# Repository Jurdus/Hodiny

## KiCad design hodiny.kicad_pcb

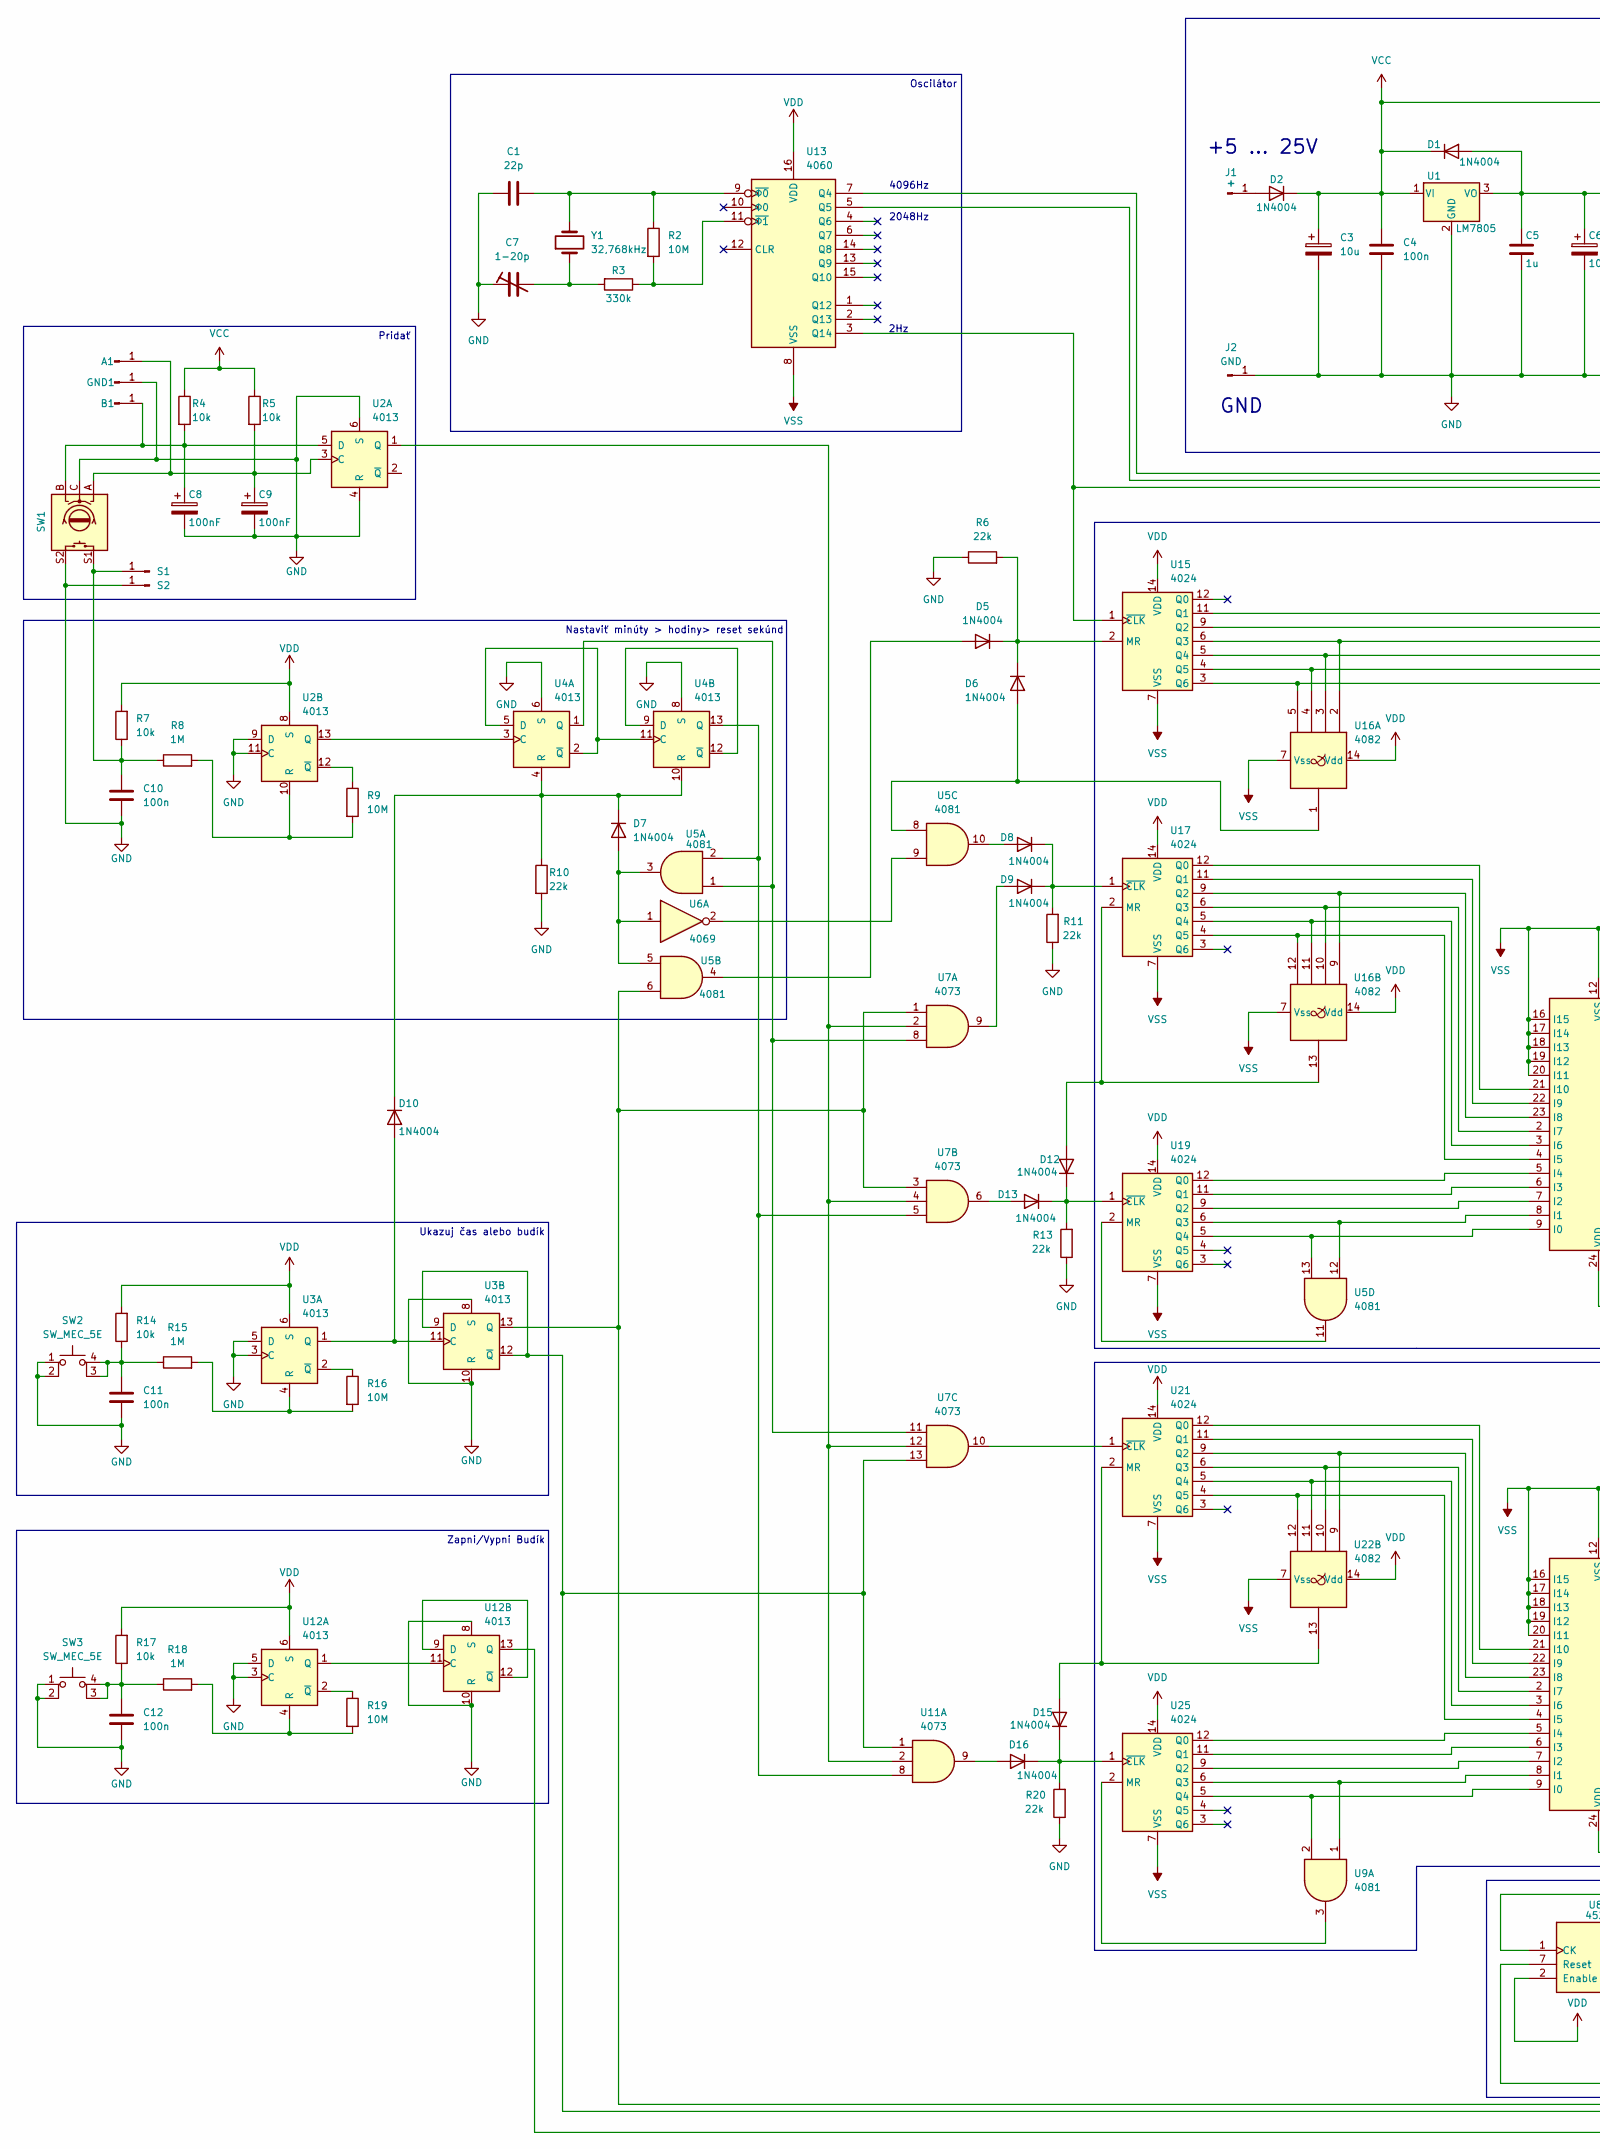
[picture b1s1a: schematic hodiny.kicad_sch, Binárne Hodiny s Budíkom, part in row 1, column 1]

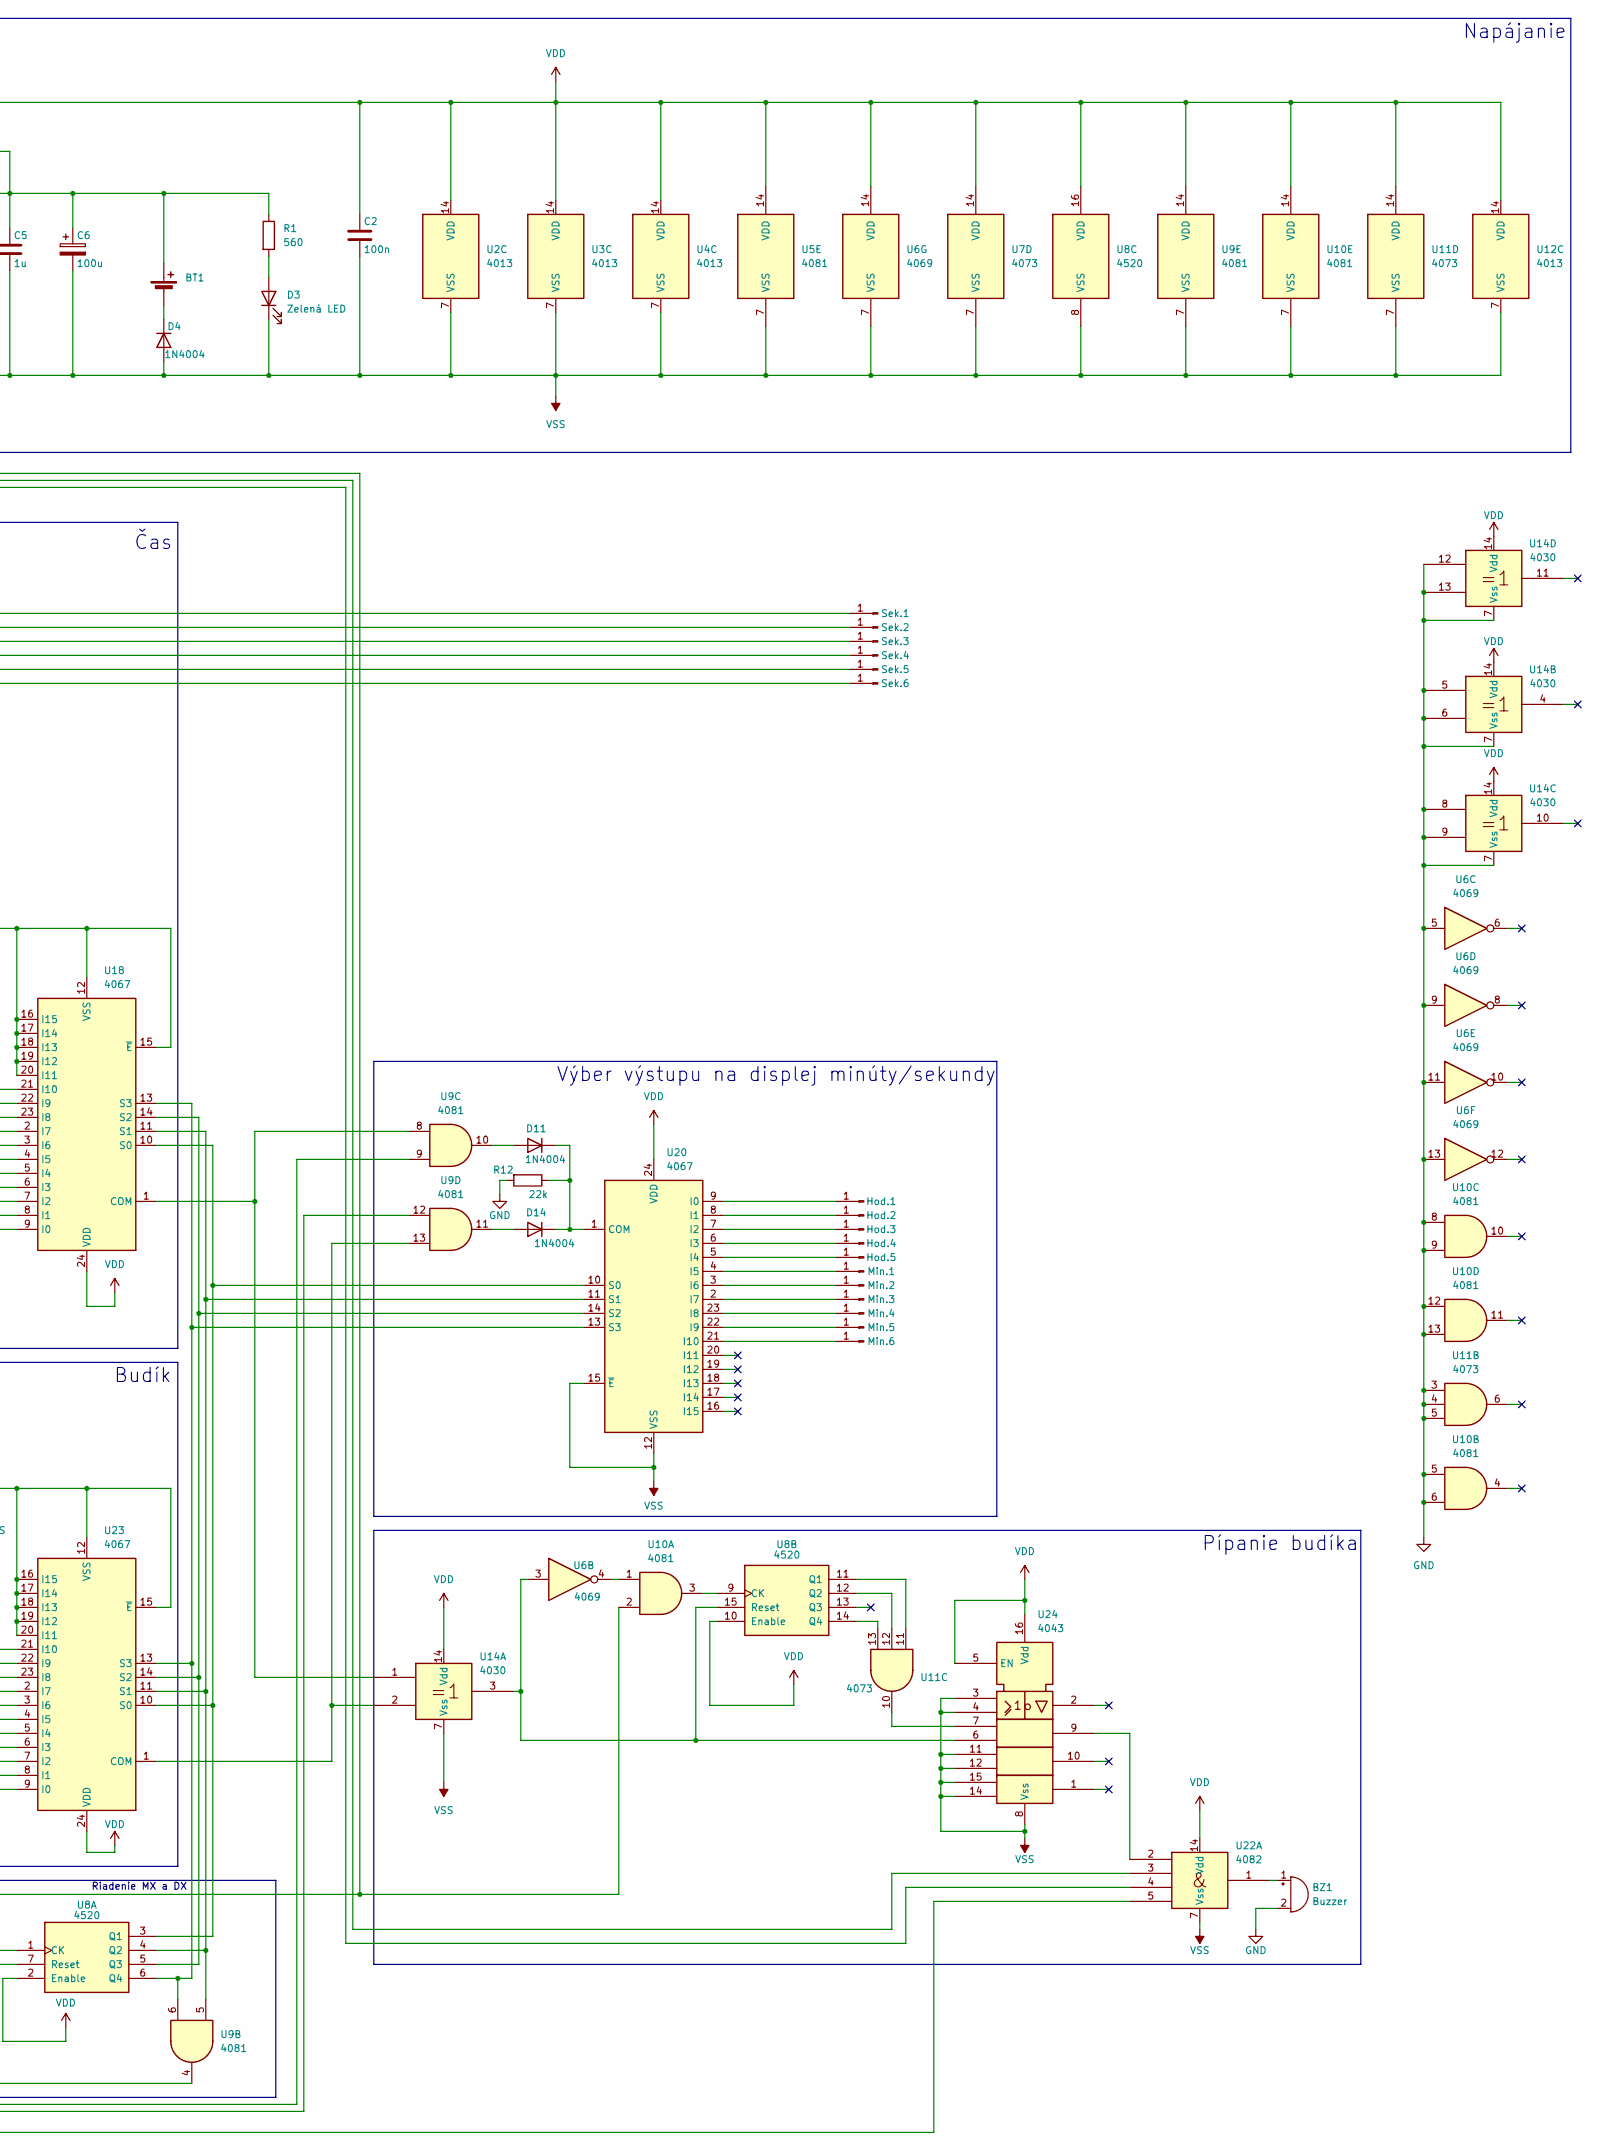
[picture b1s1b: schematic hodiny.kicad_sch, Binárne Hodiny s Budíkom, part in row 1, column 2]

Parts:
A1: A; pad
B1: B; pad
BT1: SolderWire-1sqmm_1x02_P7.8mm_D1.4mm_OD3.9mm
BZ1: Buzzer; Buzzer D12.6, P5.00
C1: 22p; C_1206_3216Metric
C2, C4: 100n; C_Disc_D4.3mm_W1.9mm_P5.00mm
C3: 10u; CP_Radial_D5.0mm_P2.00mm
C5: 1u; C_Disc_D4.3mm_W1.9mm_P5.00mm
C6: 100u; CP_Radial_D5.0mm_P2.00mm
C7: 1-20p; L_Radial_D6.0mm_P4.00mm
C8, C9: 100nF; CP_Radial_D5.0mm_P2.00mm
C10, C11, C12: 100n; C_1206_3216Metric
D1, D2, D4, D5, D6, D7, D8, D9, D10, D11, D12, D13, D14, D15, D16: 1N4004; D_DO-41_SOD81_P12.70mm_Horizontal
D3: Zelená LED; LED_D5.0mm
GND1: C; pad
Hod.1, Hod.2, Hod.3, Hod.4, Hod.5: Conn_01x01_Pin; pad
J1: +; pad
J2: GND; pad
Min.1, Min.2, Min.3, Min.4, Min.5, Min.6: Conn_01x01_Pin; pad
R1: 560; R_1206_3216Metric
R2, R9, R16, R19: 10M; R_1206_3216Metric
R3: 330k; R_1206_3216Metric
R4, R5, R7, R14, R17: 10k; R_1206_3216Metric
R6, R10, R11, R12, R13, R20: 22k; R_Axial_DIN0309_L9.0mm_D3.2mm_P15.24mm_Horizontal
R8, R15, R18: 1M; R_1206_3216Metric
S1: C; pad
S2: A; pad
SW1: (no value)
SW2, SW3: SW_MEC_5E; button placeholder
Sek.1, Sek.2, Sek.3, Sek.4, Sek.5, Sek.6: Conn_01x01_Pin; pad
U1: LM7805; TO-220-3_Vertical
U2, U3, U4, U12: 4013; DIP-14_W7.62mm_LongPads
U5, U9, U10: 4081; DIP-14_W7.62mm_LongPads
U6: 4069; DIP-14_W7.62mm_LongPads
U7, U11: 4073; DIP-14_W7.62mm_LongPads
U8: 4520; DIP-16_W7.62mm_LongPads
U13: 4060; DIP-16_W7.62mm_LongPads
U14: 4030; DIP-14_W7.62mm_LongPads
U15, U17, U19, U21, U25: 4024; DIP-14_W7.62mm_LongPads
U16, U22: 4082; DIP-14_W7.62mm_LongPads
U18, U20, U23: 4067; SOIC-24W_7.5x15.4mm_P1.27mm
U24: 4043; DIP-24_W7.62mm_LongPads
Y1: 32,768kHz; Crystal_DS26_D2.0mm_L6.0mm_Horizontal

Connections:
GND: BZ1.2 (-), C1.1, C2.2, C3.2, C4.2, C5.2, C6.2, C7.1, C8.2, C9.2, C10.2, C11.2, C12.2, D3.1 (K), D4.2 (A), GND1.1, J2.1, R6.1, R10.2, R11.1, R12.2, R13.1, R20.1, S2.1, SW1.C, SW1.S2, SW2.1, SW2.2, SW3.1, SW3.2, U1.2 (GND), U2.4 (R), U2.6 (S), U2.7 (VSS), U2.9 (D), U2.11 (C), U3.3 (C), U3.5 (D), U3.7 (VSS), U3.8 (S), U3.10 (R), U4.6 (S), U4.7 (VSS), U4.8 (S), U5.7 (VSS), U6.5, U6.7 (VSS), U6.9, U6.11, U6.13, U7.7 (VSS), U8.8 (VSS), U9.7 (VSS), U10.5, U10.6, U10.7 (VSS), U10.8, U10.9, U10.12, U10.13, U11.3, U11.4, U11.5, U11.7 (VSS), U12.3 (C), U12.5 (D), U12.7 (VSS), U12.8 (S), U12.10 (R), U13.8 (VSS), U14.5, U14.6, U14.7 (Vss), U14.8, U14.9, U14.12, U14.13, U15.7 (VSS), U16.7 (Vss), U17.7 (VSS), U18.12 (VSS), U18.15 (~E), U18.16 (I15), U18.17 (I14), U18.18 (I13), U18.19 (I12), U18.20 (I11), U19.7 (VSS), U20.12 (VSS), U20.15 (~E), U21.7 (VSS), U22.7 (Vss), U23.12 (VSS), U23.15 (~E), U23.16 (I15), U23.17 (I14), U23.18 (I13), U23.19 (I12), U23.20 (I11), U24.3, U24.4, U24.8 (Vss), U24.11, U24.12, U24.14, U24.15, U25.7 (VSS)
unnamed: A1.1, C9.1, R5.2, SW1.A, U2.3 (C)
unnamed: B1.1, C8.1, R4.2, SW1.B, U2.5 (D)
unnamed: BT1.1 (+), C5.1, C6.1, D1.2 (A), R1.1, U1.3 (VO)
unnamed: BT1.2 (-), D4.1 (K)
unnamed: BZ1.1 (+), U22.1
unnamed: C7.2, R3.2, Y1.1
unnamed: D2.2 (A), J1.1
unnamed: D3.2 (A), R1.2
unnamed: D5.2 (A), U5.4
unnamed: D5.1 (K), D6.1 (K), R6.2, U15.2 (MR)
unnamed: D6.2 (A), U5.8, U16.1
unnamed: D7.2 (A), U5.3, U5.5, U6.1
unnamed: D8.2 (A), U5.10
unnamed: D8.1 (K), D9.1 (K), R11.2, U17.1 (~CLK)
unnamed: D9.2 (A), U7.9
unnamed: D10.2 (A), U3.1 (Q), U3.11 (C)
unnamed: D7.1 (K), D10.1 (K), R10.1, U4.4 (R), U4.10 (R)
unnamed: D11.2 (A), U9.10
unnamed: D11.1 (K), D14.1 (K), R12.1, U20.1 (COM)
unnamed: D12.2 (A), U16.13, U17.2 (MR)
unnamed: D12.1 (K), D13.1 (K), R13.2, U19.1 (~CLK)
unnamed: D13.2 (A), U7.6
unnamed: D14.2 (A), U9.11
unnamed: D15.2 (A), U21.2 (MR), U22.13
unnamed: D15.1 (K), D16.1 (K), R20.2, U25.1 (~CLK)
unnamed: D16.2 (A), U11.9
unnamed: Hod.1.1, U20.9 (I0)
unnamed: Hod.2.1, U20.8 (I1)
unnamed: Hod.3.1, U20.7 (I2)
unnamed: Hod.4.1, U20.6 (I3)
unnamed: Hod.5.1, U20.5 (I4)
unnamed: Min.1.1, U20.4 (I5)
unnamed: Min.2.1, U20.3 (I6)
unnamed: Min.3.1, U20.2 (I7)
unnamed: Min.4.1, U20.23 (I8)
unnamed: Min.5.1, U20.22 (I9)
unnamed: Min.6.1, U20.21 (I10)
unnamed: C10.1, R7.1, R8.1, S1.1, SW1.S1
unnamed: C11.1, R14.1, R15.1, SW2.3 (K), SW2.4 (A)
unnamed: C12.1, R17.1, R18.1, SW3.3 (K), SW3.4 (A)
unnamed: Sek.1.1, U15.11 (Q1)
unnamed: Sek.2.1, U15.9 (Q2)
unnamed: Sek.3.1, U15.6 (Q3), U16.2
unnamed: Sek.4.1, U15.5 (Q4), U16.3
unnamed: Sek.5.1, U15.4 (Q5), U16.4
unnamed: Sek.6.1, U15.3 (Q6), U16.5
unnamed: U2.1 (Q), U7.2, U7.4, U7.12, U11.2
unnamed: U2.13 (Q), U4.3 (C)
unnamed: R8.2, R9.2, U2.10 (R)
unnamed: R9.1, U2.12 (~Q)
unnamed: R15.2, R16.2, U3.4 (R)
unnamed: R16.1, U3.2 (~Q)
unnamed: U3.9 (D), U3.12 (~Q), U7.13, U9.12, U11.1
unnamed: U3.13 (Q), U5.6, U7.1, U7.3, U9.9
unnamed: U4.2 (~Q), U4.5 (D), U4.11 (C)
unnamed: U4.1 (Q), U5.1, U7.8, U7.11
unnamed: U4.9 (D), U4.12 (~Q)
unnamed: U4.13 (Q), U5.2, U7.5, U11.8
unnamed: U5.9, U6.2
unnamed: U8.7 (Reset), U9.4
unnamed: U8.9 (CK), U10.3
unnamed: U8.11 (Q1), U11.11
unnamed: U8.12 (Q2), U11.12
unnamed: U8.14 (Q4), U11.13
unnamed: U6.3, U8.15 (Reset), U14.3, U24.6
unnamed: U6.4, U10.1
unnamed: U11.10, U24.7
unnamed: U12.1 (Q), U12.11 (C)
unnamed: R18.2, R19.2, U12.4 (R)
unnamed: R19.1, U12.2 (~Q)
unnamed: U12.9 (D), U12.12 (~Q)
unnamed: U12.13 (Q), U22.5
unnamed: U8.1 (CK), U10.2, U13.7 (Q4)
unnamed: U13.5 (Q5), U22.3
unnamed: U13.3 (Q14), U15.1 (~CLK), U22.4
unnamed: C1.2, R2.1, U13.9 (~Φ0), Y1.2
unnamed: R2.2, R3.1, U13.11 (~Φ1)
unnamed: U17.12 (Q0), U18.21 (I10)
unnamed: U17.11 (Q1), U18.22 (I9)
unnamed: U16.9, U17.9 (Q2), U18.23 (I8)
unnamed: U16.10, U17.6 (Q3), U18.2 (I7)
unnamed: U16.11, U17.5 (Q4), U18.3 (I6)
unnamed: U16.12, U17.4 (Q5), U18.4 (I5)
unnamed: U9.8, U14.1, U18.1 (COM)
unnamed: U5.13, U18.9 (I0), U19.5 (Q4)
unnamed: U5.12, U18.8 (I1), U19.6 (Q3)
unnamed: U18.7 (I2), U19.9 (Q2)
unnamed: U18.6 (I3), U19.11 (Q1)
unnamed: U18.5 (I4), U19.12 (Q0)
unnamed: U8.3 (Q1), U18.10 (S0), U20.10 (S0), U23.10 (S0)
unnamed: U8.4 (Q2), U9.5, U18.11 (S1), U20.11 (S1), U23.11 (S1)
unnamed: U8.5 (Q3), U18.14 (S2), U20.14 (S2), U23.14 (S2)
unnamed: U8.6 (Q4), U9.6, U18.13 (S3), U20.13 (S3), U23.13 (S3)
unnamed: U5.11, U19.2 (MR)
unnamed: U21.12 (Q0), U23.21 (I10)
unnamed: U21.11 (Q1), U23.22 (I9)
unnamed: U21.9 (Q2), U22.9, U23.23 (I8)
unnamed: U21.6 (Q3), U22.10, U23.2 (I7)
unnamed: U21.5 (Q4), U22.11, U23.3 (I6)
unnamed: U21.4 (Q5), U22.12, U23.4 (I5)
unnamed: U7.10, U21.1 (~CLK)
unnamed: U22.2, U24.9
unnamed: U9.13, U14.2, U23.1 (COM)
unnamed: U9.2, U23.9 (I0), U25.5 (Q4)
unnamed: U9.1, U23.8 (I1), U25.6 (Q3)
unnamed: U23.7 (I2), U25.9 (Q2)
unnamed: U23.6 (I3), U25.11 (Q1)
unnamed: U23.5 (I4), U25.12 (Q0)
unnamed: U9.3, U25.2 (MR)
VCC: C2.1, C3.1, C4.1, D1.1 (K), D2.1 (K), R4.1, R5.1, R7.2, R14.2, R17.2, U1.1 (VI), U2.8 (S), U2.14 (VDD), U3.6 (S), U3.14 (VDD), U4.14 (VDD), U5.14 (VDD), U6.14 (VDD), U7.14 (VDD), U8.2 (Enable), U8.10 (Enable), U8.16 (VDD), U9.14 (VDD), U10.14 (VDD), U11.14 (VDD), U12.6 (S), U12.14 (VDD), U13.16 (VDD), U14.14 (Vdd), U15.14 (VDD), U16.14 (Vdd), U17.14 (VDD), U18.24 (VDD), U19.14 (VDD), U20.24 (VDD), U21.14 (VDD), U22.14 (Vdd), U23.24 (VDD), U24.5 (EN), U24.16 (Vdd), U25.14 (VDD)

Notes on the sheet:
Oscilátor
Pridať
4096Hz
Riadenie MX a DX
+5 ... 25V
Nastaviť minúty > hodiny> reset sekúnd
Zapni/Vypni Budík
Napájanie
Budík
2048Hz
2Hz
Pípanie budíka
Čas
Ukazuj čas alebo budík
GND
Výber výstupu na displej minúty/sekundy

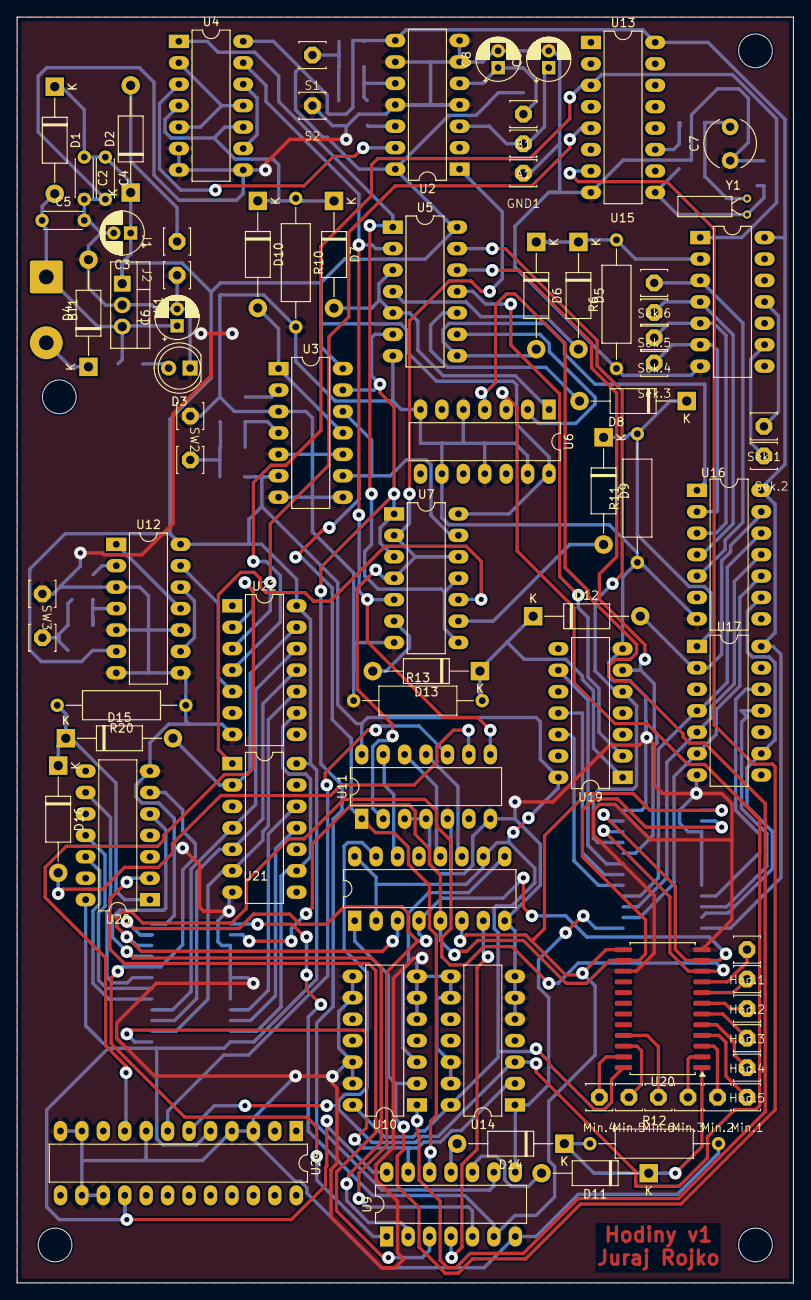
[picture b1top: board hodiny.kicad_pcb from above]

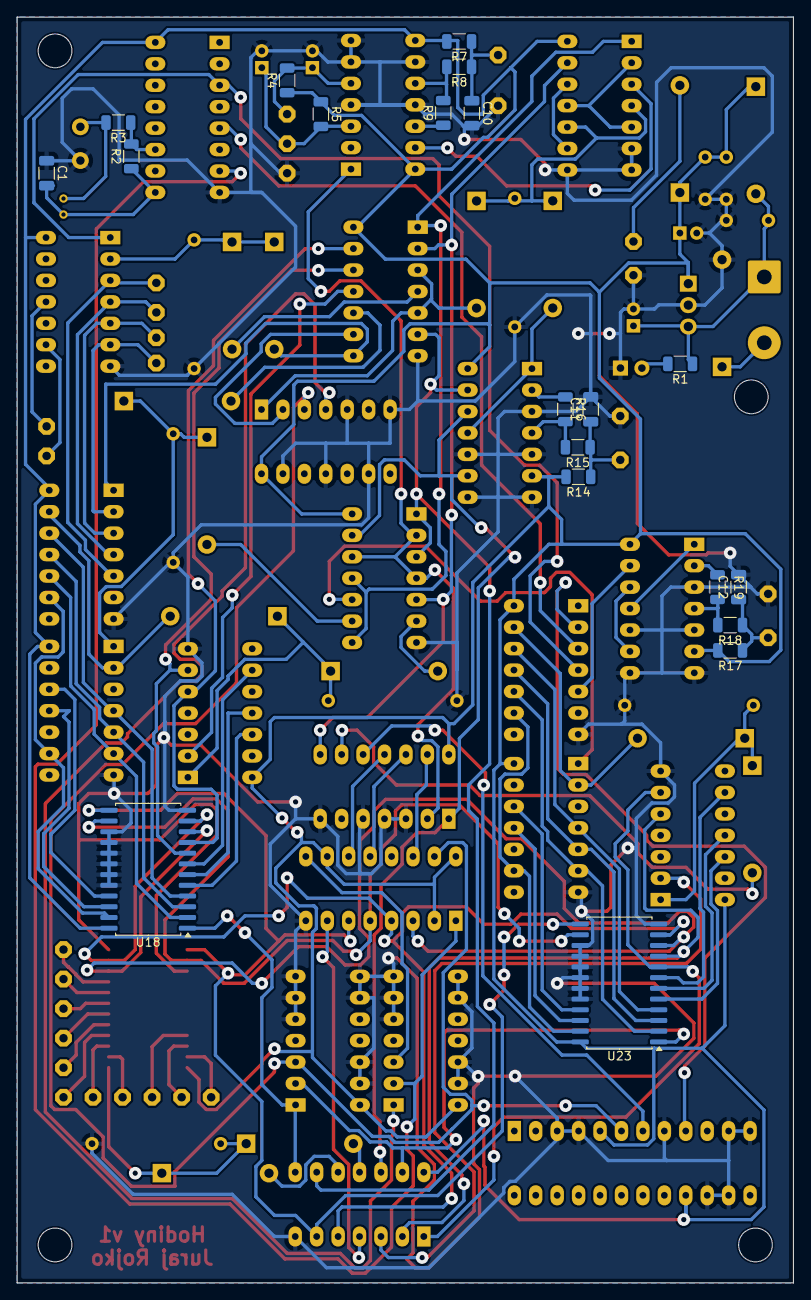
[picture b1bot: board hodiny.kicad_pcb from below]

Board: 2 copper layers, 92.0 x 150.0 mm, 101 parts (20 on the bottom side), 110 nets.

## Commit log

2025-02-04 vymazavam zbytočnu schemu
